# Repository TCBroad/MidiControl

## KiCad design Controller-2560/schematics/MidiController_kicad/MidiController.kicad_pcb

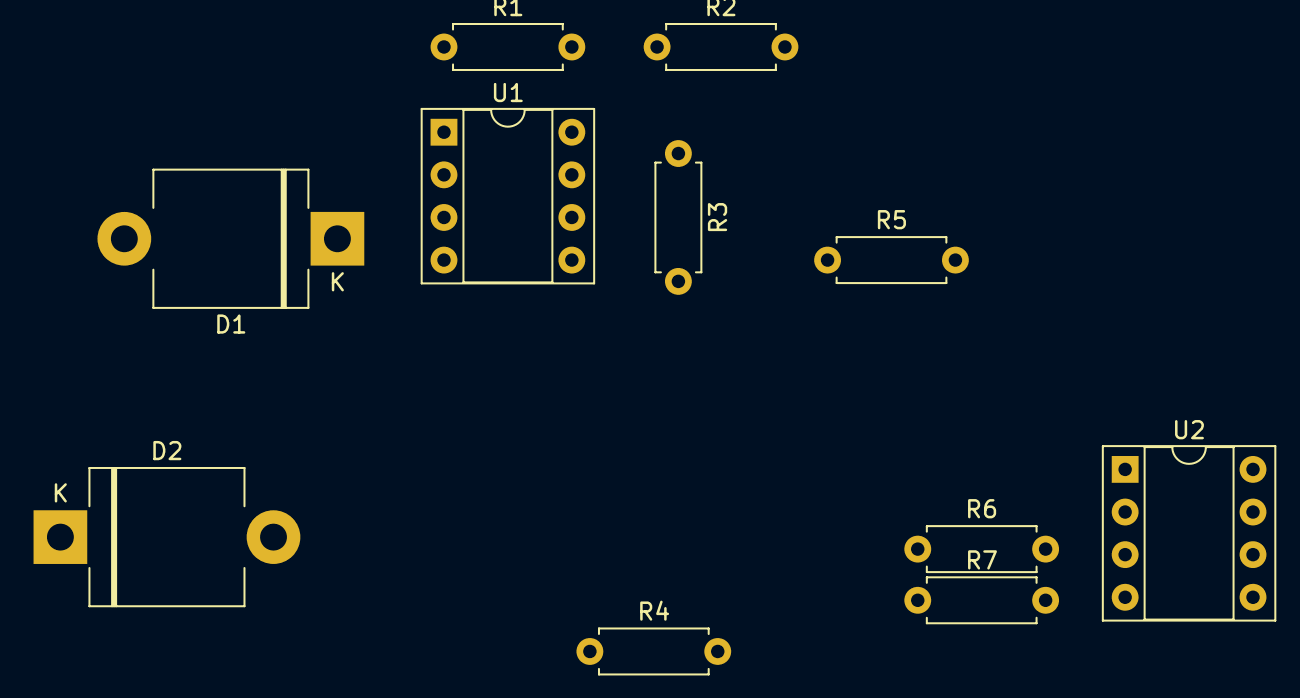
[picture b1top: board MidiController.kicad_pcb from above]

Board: 2 copper layers, 11 parts (0 on the bottom side), 10 nets, no tracks yet.

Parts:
D1, D2: DIODE; D_5KPW_P12.70mm_Horizontal
R1, R2, R3, R4, R5, R6, R7: R; R_Axial_DIN0207_L6.3mm_D2.5mm_P7.62mm_Horizontal
U1, U2: 6N138; DIP-8_W7.62mm_Socket

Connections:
+5V: R2.1, R5.1, R7.1, U1.8, U2.8
/MIDI1_TX: D1.1, U1.3
/MIDI2_TX: D2.1, U2.3
GND: R3.2, R6.2, U1.5, U2.5
unnamed: D1.2, R1.1, U1.2
unnamed: D2.2, R4.1, U2.2
unnamed: R5.2, U2.6
unnamed: R2.2, U1.6
unnamed: R3.1, U1.7
unnamed: R6.1, U2.7

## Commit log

2018-10-09 Added existing code
2018-10-11 fixed non-preset selection added LEDs
2018-10-20 added schematic (WIP) changed serial port, refactoring
2018-10-21 Added scenes + status LED
2018-10-21 Handle scenes properly Keypad layout changed MIDI Merge works
2018-10-22 Added mute Refactoring Better led output
2018-10-22 Refactoring
2018-10-27 Updated schematic
2018-11-02 Added led display output
2018-11-02 added decimal point flash on midi input
2018-11-05 added sysex read + axe fx funcs
2018-11-06 bugfixes after testing with actual hardware
2018-11-08 Got fresh project working in clion
2018-11-09 Started pulling old code out into classes
2018-11-11 Added methods to header
2018-11-11 Added implementations of class
2018-11-13 Implemented various hal methods
2018-11-18 Refactoring, added tcl5947 support, removed String usage
2019-07-14 Implemented remaining methods, changed types - update to pio 4
2019-07-19 Big refactor, basically rewrite
2020-07-27 [hardware] Everything runs on SPI. Moved to stm32
